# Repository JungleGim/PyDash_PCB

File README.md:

# PyDash_PCB - Information
This readme covers the printed circuit board or PCB portion of the PyDash. For the App design, Enclosure design, or OS design, see the below repositories:
- [PyDash_OS](https://github.com/JungleGim/PyDash_OS)
- [PyDash_App](https://github.com/JungleGim/PyDash_App)
- [PyDash_PCB](https://github.com/JungleGim/PyDash_PCB)
- [PyDash_Enclosure](https://github.com/JungleGim/PyDash_Enclosure)
- [PyDash_Builder](https://github.com/JungleGim/PyDash_Builder)

## Introduction
The PyDash_PCB is a daughter board that contains the hardware required for a rPi compute module (CM4) to function as a processor to display information on a 7in screen.

Additional details on the design considerations, required packages, and key features are included in the "Methodology" section of this readme.

# Project Status
## Revlog
- Rev 0: 06/02/2024
	- Initial issue
- Rev1a: 05/19/2025
	- Fixed button numbering to be appropriate when viewing the screen
- Rev2a: 02/15/2026
	- updates realted to Rev2.0a rebuild - includes new features and code architecture
	- Added micro SD socket for users to load dash config files
	- Updated USB port to USBC
	- Removed touch lines from screen and removed USB mux - no plans to utilize touch in future

# Methodology
## History
TBD: quick detail starting with the arduino + daughter board on the 5in display as a proof of concept

## Key Considerations and Constraints
The following sections are some notes on the various considerations or any constraints when designing the display.

### Power Supply
As built, with the sourced display and components in the BOM, the display uses approximately 350-400mA when operation, at 100% backlight.

### Display
The chosen display is a 7inch 1024x600 IPS display sourced from waveshare [link](https://www.waveshare.com/70h-1024600.htm?sku=22671). The display is fastened to the carrier PCB via double-sided foam tape. The 40pin FPC jack directly connects to the HDMI output from the CM4.

To control the backlight via PWM, drive the "BL_en" pin high. The PWM signal is scaled from 1024 (100%) to 0 (0) for brightest to darkest.

Any HDMI compatable display should be able to be used with this design. While the FPC cable was a design choice, any other HDMI connection should be appropriate, depending on the chosen display.

Additional considerations for the HDMI hardware and driver configuration is contained in the "PyDash OS" readme.

#### PCB stackup
JLC PCB stackups for TDMS impedence considerations

* Chosen stackup: JLC04121H-3313 – 1oz (0.035mm) outer layer
	+ Chosen stackup option
	+ Top to inner 1 and inner 2 to bot separation is 0.1
	+ requires 0.18mm trace width for single-ended impedence target
	+ 0.3mm separation for differential impedence target

* Other available options with calculated requirements
	+ JLC04121H-7628 - 1oz (0.035mm) outer layer
		* Top to inner 1 and inner 2 to bot separation is 0.2
		* requires 0.3mm trace width for single-ended impedence target
		* 0.25mm separation for differential impedence target
	+ JLC04121H-1080 Stackup – 1oz (0.035mm) outer layer
		* Top to inner 1 and inner 2 to bot separation is 0.0764
		* requires 0.13mm width
		* 0.20mm separation for differential impedence target

# Known bugs and bug fixes
No current known bugs

# FAQ section
No current FAQ

# Copyright and licensing information
## GNU GPLv3
This program is free software: you can redistribute it and/or modify it under the terms of the GNU General Public License as published by the Free Software Foundation, either version 3 of the License, or (at your option) any later version.

This program is distributed in the hope that it will be useful, but WITHOUT ANY WARRANTY; without even the implied warranty of MERCHANTABILITY or FITNESS FOR A PARTICULAR PURPOSE.  See the
GNU General Public License for more details.

You should have received a copy of the GNU General Public License along with this program.  If not, see <https://www.gnu.org/licenses/>.

## Additional disclaimer
The information included is provided "as is", without warranty of any kind, express or implied, including but not limited to the warranties of merchantability, fitness for a particular purpose and non-infringement. In no event shall the authors or copyright holders be liable for any claim, damages or other liability, whether in an action of contract, tort or otherwise, arising from, out of or in connection with the software or the use or other dealings in the software or tools included in this repository.

# General Notes and References
While I am an engineer by trade, my area of focus is not computer architecture or system engineering. Likely some people have already looked at various aspects of the codebase and just shook their heads. That being said, I've compiled a list of considerations and notes for the project that have helped me along the way. These are listed below, in no particular order.

## References
Throughout the project, I have used many references, related to various aspects/items of the project. These are all compiled in the list below, in no particular order
- TBD any notable references

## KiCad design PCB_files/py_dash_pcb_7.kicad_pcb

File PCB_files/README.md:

# PyDash_PCB - Information
This readme covers the printed circuit board or PCB portion of the PyDash. For the App design, Enclosure design, or OS design, see the below repositories:
- PyDash_OS
- PyDash_App
- PyDash_Enclosure

## Introduction
The PyDash_PCB is a daughter board that contains the hardware required for a rPi compute module (CM4) to function as a processor to display information on a 7in screen.

Additional details on the design considerations, required packages, and key features are included in the "Methodology" section of this readme.

# Project Status
## Revlog
- Rev 0: 06/02/2024
	- Initial issue
- Rev1a: 05/19/2025
	- Fixed button numbering to be appropriate when viewing the screen
- Rev2a: 02/15/2026
	- updates realted to Rev2.0a rebuild - includes new features and code architecture
	- Added micro SD socket for users to load dash config files
	- Updated USB port to USBC
	- Removed touch lines from screen and removed USB mux - no plans to utilize touch in future
	
## Future Development
The below is a list of wants/needs for future revisions; loosely listed in order of importance.

- USB port is routed but not functional; app design requires additional features
- Update mounting holes for CM4 to solder pads for use of solder-on standoffs to attach CM4
- Scope out board assembly cost

# Methodology
## History
TBD: quick detail starting with the arduino + daughter board on the 5in display as a proof of concept

## Key Considerations and Constraints
TBD: power supply and other notes (approx 350mA draw when running)
TBD: PWM backlight notes
TBD: display notes (especially different considerations)

# Known bugs and bug fixes
No current known bugs

# FAQ section
No current FAQ

# Copyright and licensing information
## GNU GPLv3
This program is free software: you can redistribute it and/or modify it under the terms of the GNU General Public License as published by the Free Software Foundation, either version 3 of the License, or (at your option) any later version.

This program is distributed in the hope that it will be useful, but WITHOUT ANY WARRANTY; without even the implied warranty of MERCHANTABILITY or FITNESS FOR A PARTICULAR PURPOSE.  See the
GNU General Public License for more details.

You should have received a copy of the GNU General Public License along with this program.  If not, see <https://www.gnu.org/licenses/>.

## Additional disclaimer
The information included is provided "as is", without warranty of any kind, express or implied, including but not limited to the warranties of merchantability, fitness for a particular purpose and non-infringement. In no event shall the authors or copyright holders be liable for any claim, damages or other liability, whether in an action of contract, tort or otherwise, arising from, out of or in connection with the software or the use or other dealings in the software or tools included in this repository.

# General Notes and References
While I am an engineer by trade, my area of focus is not computer architecture or system engineering. Likely some people have already looked at various aspects of the codebase and just shook their heads. That being said, I've compiled a list of considerations and notes for the project that have helped me along the way. These are listed below, in no particular order.

## References
Throughout the project, I have used many references, related to various aspects/items of the project. These are all compiled in the list below, in no particular order
- TBD any notable references

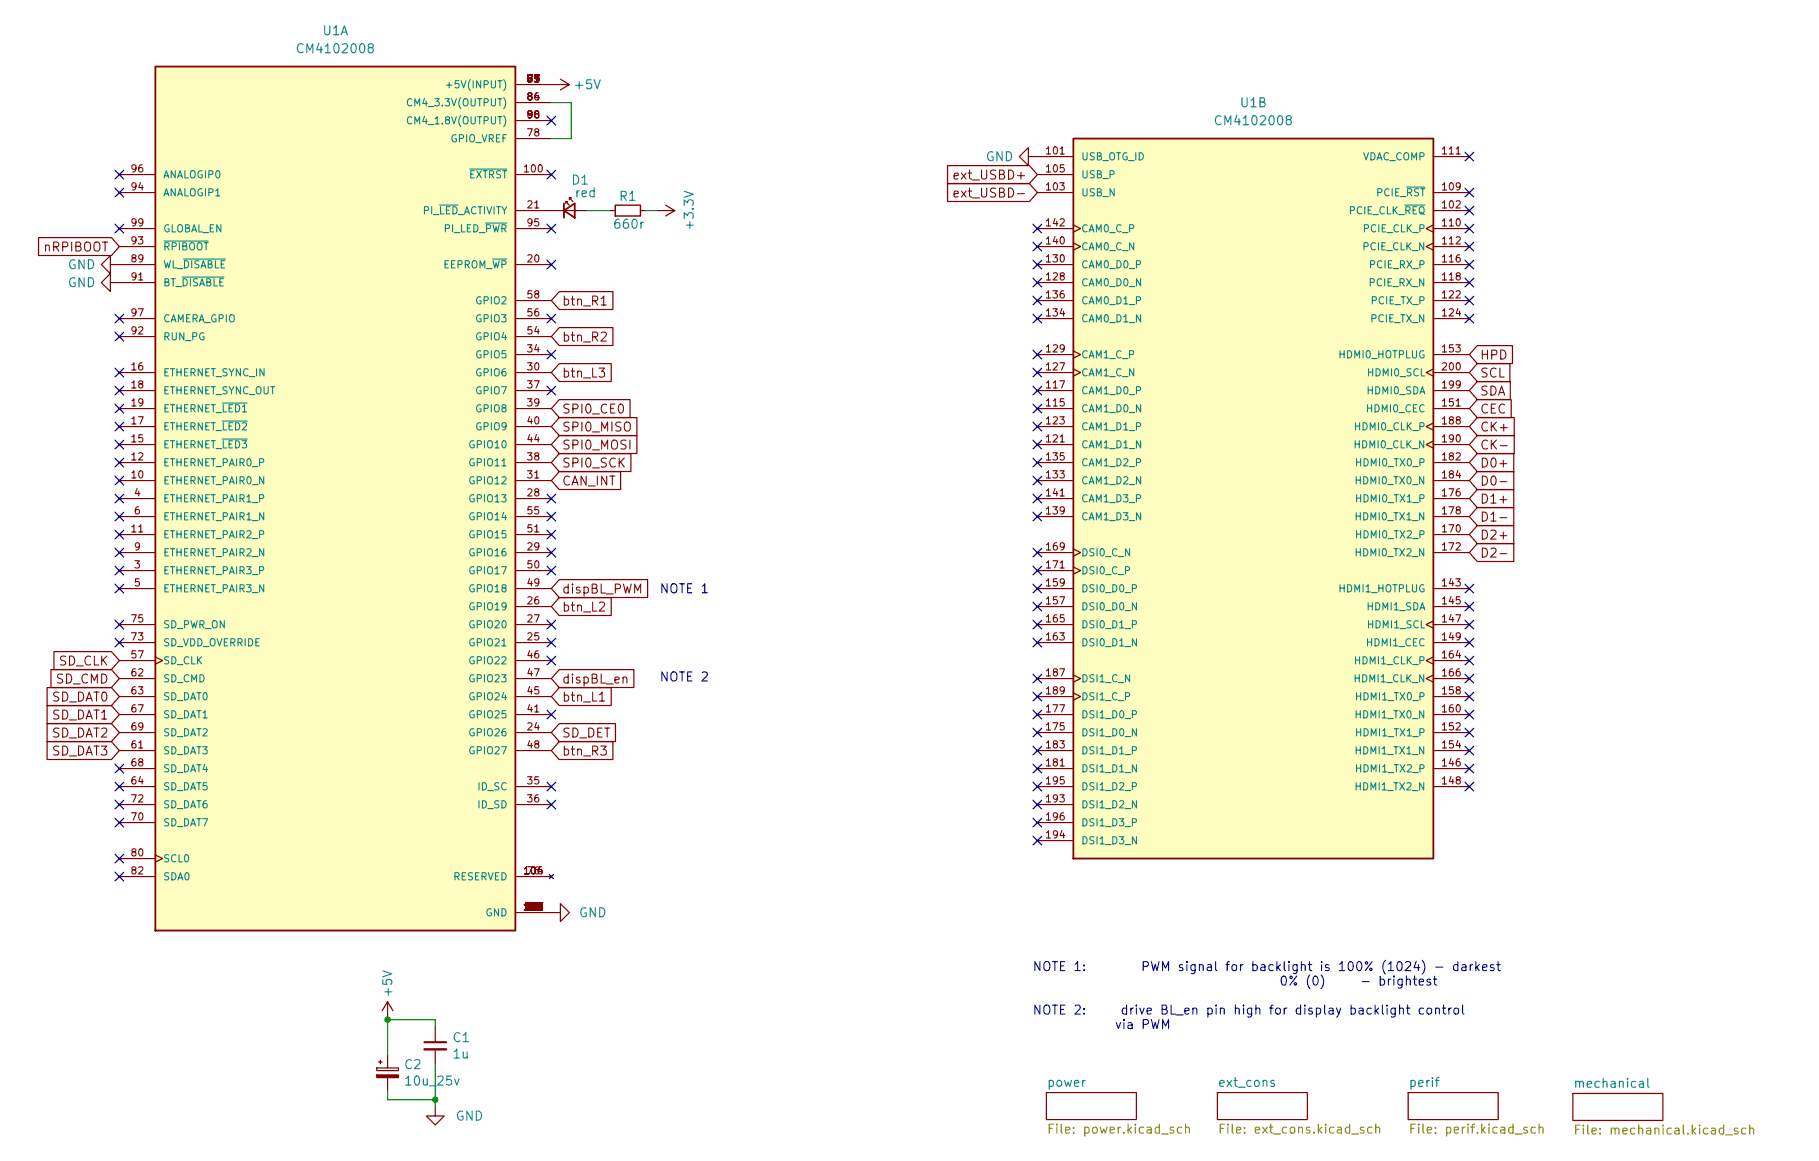
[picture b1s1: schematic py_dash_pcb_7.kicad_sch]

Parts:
C1: 1u; C_0805_2012Metric; MPN C0805C105M3RACTU
C2: 10u_25v; CP_EIA-3528-21_Kemet-B; MPN T495B106K025ATE750
D1: red; LED_0805_2012Metric; MPN 150080RS75000
R1: 660r; R_0805_2012Metric; MPN CRCW0805665RFKEA
U1: CM4102008; MODULE_CM4102008; PARTREV 2021-10-12

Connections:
+3.3V: R1.2; also elsewhere on the board
+5V: C1.1, C2.1, U1.77 (+5V(INPUT)), U1.79 (+5V(INPUT)), U1.81 (+5V(INPUT)), U1.83 (+5V(INPUT)), U1.85 (+5V(INPUT)), U1.87 (+5V(INPUT)); also elsewhere on the board
CAN_INT: U1.31 (GPIO12); also elsewhere on the board
CEC: U1.151 (HDMI0_CEC); also elsewhere on the board
CK+: U1.188 (HDMI0_CLK_P); also elsewhere on the board
CK-: U1.190 (HDMI0_CLK_N); also elsewhere on the board
D0+: U1.182 (HDMI0_TX0_P); also elsewhere on the board
D0-: U1.184 (HDMI0_TX0_N); also elsewhere on the board
D1+: U1.176 (HDMI0_TX1_P); also elsewhere on the board
D1-: U1.178 (HDMI0_TX1_N); also elsewhere on the board
D2+: U1.170 (HDMI0_TX2_P); also elsewhere on the board
D2-: U1.172 (HDMI0_TX2_N); also elsewhere on the board
GND: C1.2, C2.2, U1.1 (GND), U1.2 (GND), U1.7 (GND), U1.8 (GND), U1.13 (GND), U1.14 (GND), U1.22 (GND), U1.23 (GND), U1.32 (GND), U1.33 (GND), U1.42 (GND), U1.43 (GND), U1.52 (GND), U1.53 (GND), U1.59 (GND), U1.60 (GND), U1.65 (GND), U1.66 (GND), U1.71 (GND), U1.74 (GND), U1.89 (WL_~DISABLE), U1.91 (BT_~DISABLE), U1.98 (GND), U1.101 (USB_OTG_ID), U1.107 (GND), U1.108 (GND), U1.113 (GND), U1.114 (GND), U1.119 (GND), U1.120 (GND), U1.125 (GND), U1.126 (GND), U1.131 (GND), U1.132 (GND), U1.137 (GND), U1.138 (GND), U1.144 (GND), U1.150 (GND), U1.155 (GND), U1.156 (GND), U1.161 (GND), U1.162 (GND), U1.167 (GND), U1.168 (GND), U1.173 (GND), U1.174 (GND), U1.179 (GND), U1.180 (GND), U1.185 (GND), U1.186 (GND), U1.191 (GND), U1.192 (GND), U1.197 (GND), U1.198 (GND); also elsewhere on the board
HPD: U1.153 (HDMI0_HOTPLUG); also elsewhere on the board
unnamed: D1.2 (A), R1.1
unnamed: D1.1 (K), U1.21 (PI_~LED_ACTIVITY)
unnamed: U1.78 (GPIO_VREF), U1.84 (CM4_3.3V(OUTPUT)), U1.86 (CM4_3.3V(OUTPUT))
SCL: U1.200 (HDMI0_SCL); also elsewhere on the board
SDA: U1.199 (HDMI0_SDA); also elsewhere on the board
SD_CLK: U1.57 (SD_CLK); also elsewhere on the board
SD_CMD: U1.62 (SD_CMD); also elsewhere on the board
SD_DAT0: U1.63 (SD_DAT0); also elsewhere on the board
SD_DAT1: U1.67 (SD_DAT1); also elsewhere on the board
SD_DAT2: U1.69 (SD_DAT2); also elsewhere on the board
SD_DAT3: U1.61 (SD_DAT3); also elsewhere on the board
SD_DET: U1.24 (GPIO26); also elsewhere on the board
SPI0_CE0: U1.39 (GPIO8); also elsewhere on the board
SPI0_MISO: U1.40 (GPIO9); also elsewhere on the board
SPI0_MOSI: U1.44 (GPIO10); also elsewhere on the board
SPI0_SCK: U1.38 (GPIO11); also elsewhere on the board
btn_L1: U1.45 (GPIO24); also elsewhere on the board
btn_L2: U1.26 (GPIO19); also elsewhere on the board
btn_L3: U1.30 (GPIO6); also elsewhere on the board
btn_R1: U1.58 (GPIO2); also elsewhere on the board
btn_R2: U1.54 (GPIO4); also elsewhere on the board
btn_R3: U1.48 (GPIO27); also elsewhere on the board
dispBL_PWM: U1.49 (GPIO18); also elsewhere on the board
dispBL_en: U1.47 (GPIO23); also elsewhere on the board
ext_USBD+: U1.105 (USB_P); also elsewhere on the board
ext_USBD-: U1.103 (USB_N); also elsewhere on the board
nRPIBOOT: U1.93 (~RPIBOOT); also elsewhere on the board

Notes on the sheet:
NOTE 2
NOTE 1: PWM signal for backlight is 100% (1024) - darkest 0% (0) - brightest NOTE 2: drive BL_en pin high for display backlight control via PWM
NOTE 1

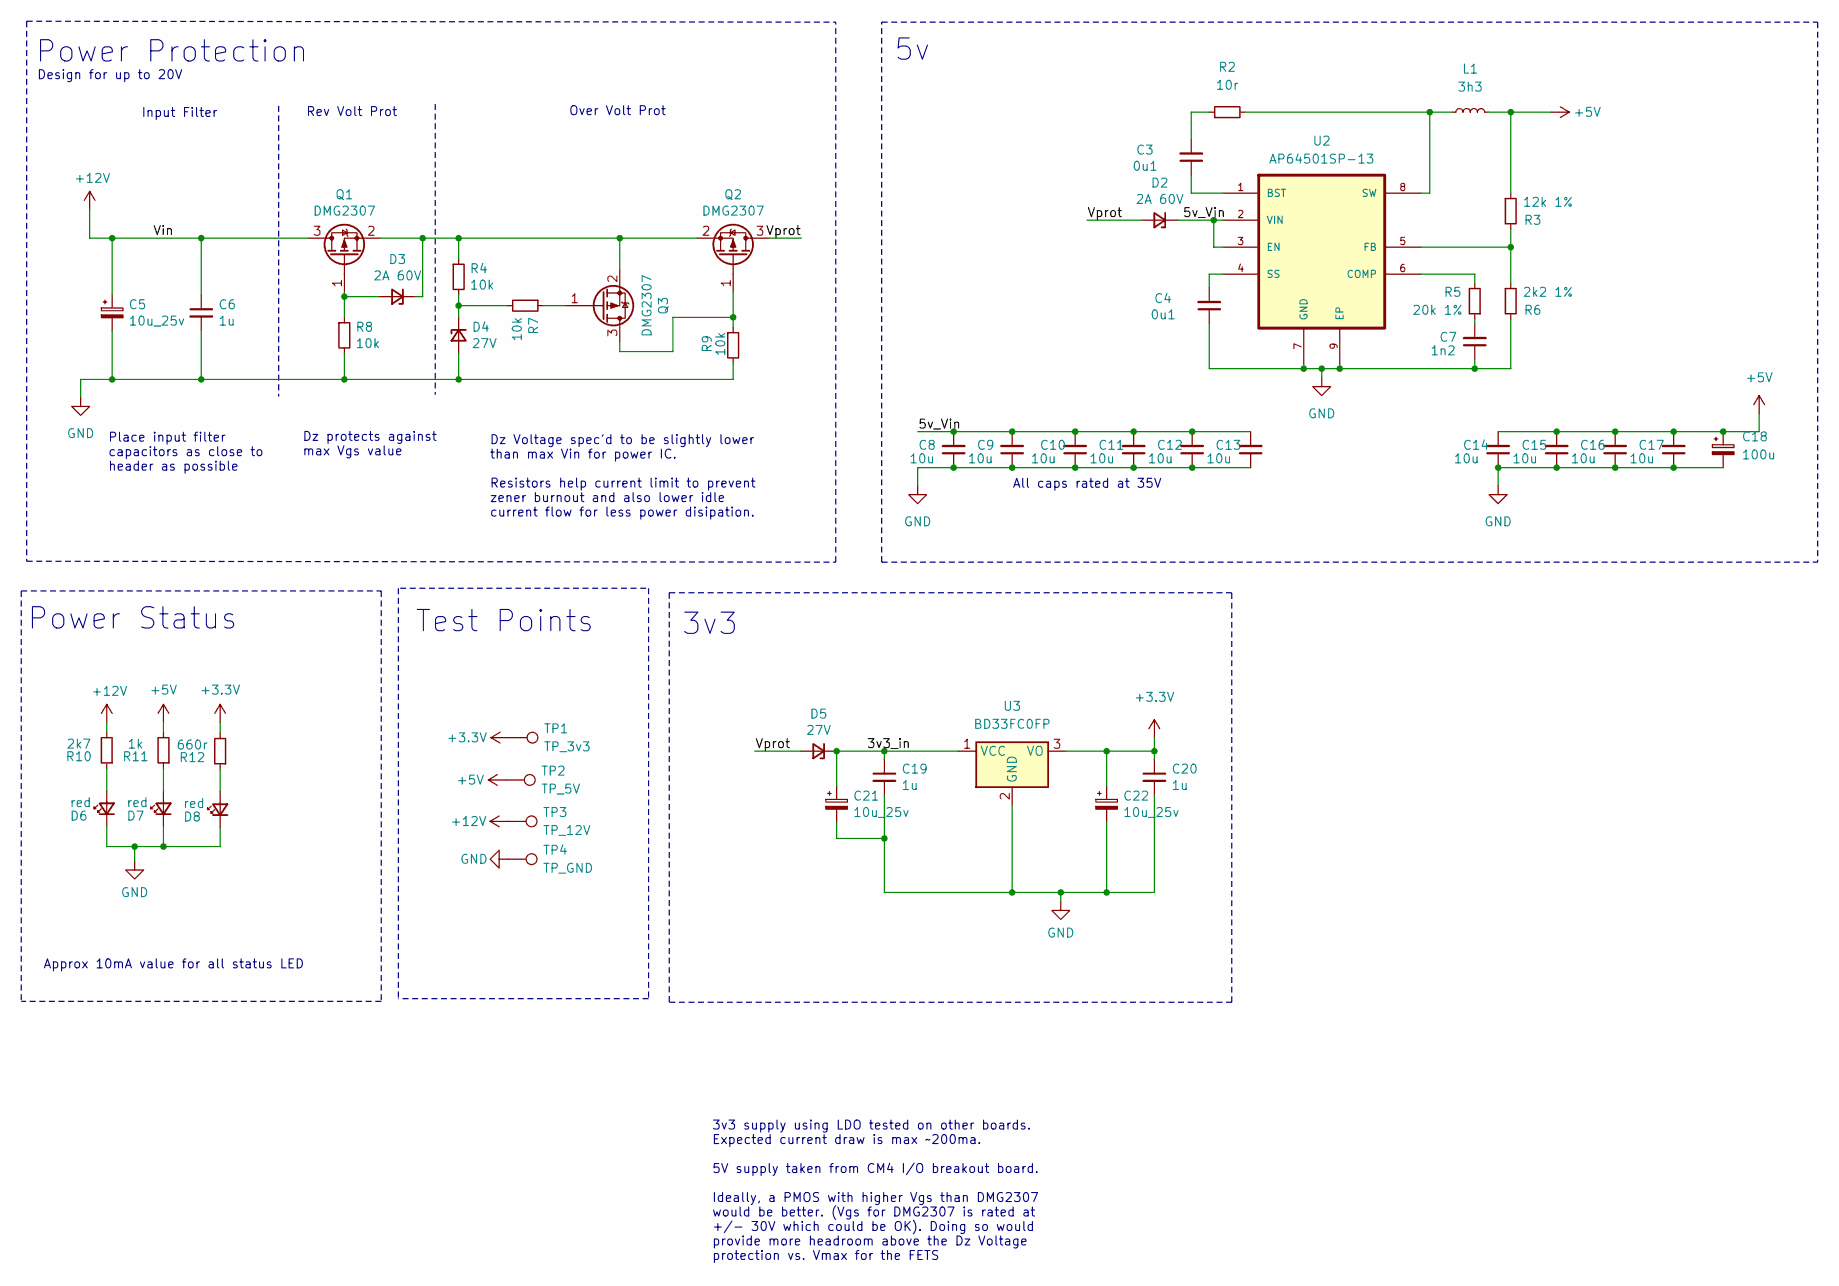
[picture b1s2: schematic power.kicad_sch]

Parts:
C3, C4: 0u1; C_0805_2012Metric; MPN C0805C104M5RACTU
C5, C21, C22: 10u_25v; CP_EIA-3528-21_Kemet-B; MPN T495B106K025ATE750
C6, C19, C20: 1u; C_0805_2012Metric; MPN C0805C105M3RACTU
C7: 1n2; C_0805_2012Metric; MPN C0805C122K5RACTU
C8, C9, C10, C11, C12, C13, C14, C15, C16, C17: 10u; C_0805_2012Metric; MPN C0805C106K4PAC
C18: 100u; CP_EIA-3528-21_Kemet-B; MPN TPSB107K010R0400
D2, D3: 2A 60V; D_SOD-123; MPN CDBMT260-HF
D4, D5: 27V; D_SOD-123; MPN MMSZ27T1G
D6, D7, D8: red; LED_0805_2012Metric; MPN 150080RS75000
L1: 3h3; L_Bourns_SRN6045TA; MPN SRN6045-3R3Y
Q1, Q2, Q3: DMG2307; SOT-23; MPN DMG2307L-7
R2: 10r; R_0805_2012Metric; MPN CRCW080510R0FKEA
R3: 12k 1%; R_0805_2012Metric; MPN CRCW080512K0FKTA
R4, R7, R8, R9: 10k; R_0805_2012Metric; MPN CRCW080510K0FKEA
R5: 20k 1%; R_0805_2012Metric; MPN CRCW080520K0FKEA
R6: 2k2 1%; R_0805_2012Metric; MPN CRCW08052K20FKEA
R10: 2k7; R_0805_2012Metric; MPN CRCW08052K70FKEA
R11: 1k; R_0805_2012Metric; MPN CRCW08051K00FKEA
R12: 660r; R_0805_2012Metric; MPN CRCW0805665RFKEA
TP1: TP_3v3; TestPoint_Pad_D1.0mm
TP2: TP_5V; TestPoint_Pad_D1.0mm
TP3: TP_12V; TestPoint_Pad_D1.0mm
TP4: TP_GND; TestPoint_Pad_D1.0mm
U2: AP64501SP-13; SOIC127P600X170-9N; MPN AP64501SP-13
U3: BD33FC0FP; TO-252-2; MPN NCV1117DT33T5G

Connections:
+3.3V: C20.1, C22.1, R12.2, TP1.1, U3.3 (VO); also elsewhere on the board
+5V: C14.2, C15.2, C16.2, C17.2, C18.1, L1.2, R3.1, R11.2, TP2.1; also elsewhere on the board
+12V: C5.1, C6.1, Q1.3 (D), R10.2, TP3.1; also elsewhere on the board
/power/3v3_in: C19.1, C21.1, D5.1 (K), U3.1 (VCC)
/power/5v_Vin: C8.2, C9.2, C10.2, C11.2, C12.2, C13.2, D2.1 (K), U2.2 (VIN), U2.3 (EN)
/power/Vprot: D2.2 (A), D5.2 (A), Q2.3 (D)
GND: C4.1, C5.2, C6.2, C7.1, C8.1, C9.1, C10.1, C11.1, C12.1, C13.1, C14.1, C15.1, C16.1, C17.1, C18.2, C19.2, C20.2, C21.2, C22.2, D4.2 (A), D6.1 (K), D7.1 (K), D8.1 (K), R6.2, R8.2, R9.2, TP4.1, U2.7 (GND), U2.9 (EP), U3.2 (GND); also elsewhere on the board
unnamed: C3.2, R2.1
unnamed: C7.2, R5.1
unnamed: D3.2 (A), Q1.1 (G), R8.1
unnamed: D3.1 (K), Q1.2 (S), Q2.2 (S), Q3.2 (S), R4.1
unnamed: D4.1 (K), R4.2, R7.2
unnamed: D6.2 (A), R10.1
unnamed: D7.2 (A), R11.1
unnamed: D8.2 (A), R12.1
unnamed: Q2.1 (G), Q3.3 (D), R9.1
unnamed: Q3.1 (G), R7.1
unnamed: C3.1, U2.1 (BST)
unnamed: R5.2, U2.6 (COMP)
unnamed: R3.2, R6.1, U2.5 (FB)
unnamed: C4.2, U2.4 (SS)
unnamed: L1.1, R2.2, U2.8 (SW)

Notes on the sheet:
Test Points
Place input filter capacitors as close to header as possible
Approx 10mA value for all status LED
Dz protects against max Vgs value
All caps rated at 35V
Design for up to 20V
Input Filter
3v3
Dz Voltage spec'd to be slightly lower than max Vin for power IC. Resistors help current limit to prevent zener burnout and also lower idle current flow for less power disipation.
Power Status
3v3 supply using LDO tested on other boards. Expected current draw is max ~200ma. 5V supply taken from CM4 I/O breakout board. Ideally, a PMOS with higher Vgs than DMG2307 would be better. (Vgs for DMG2307 is rated at +/- 30V which could be OK). Doing so would provide more headroom above the Dz Vol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
Rev Volt Prot
Over Volt Prot
Power Protection

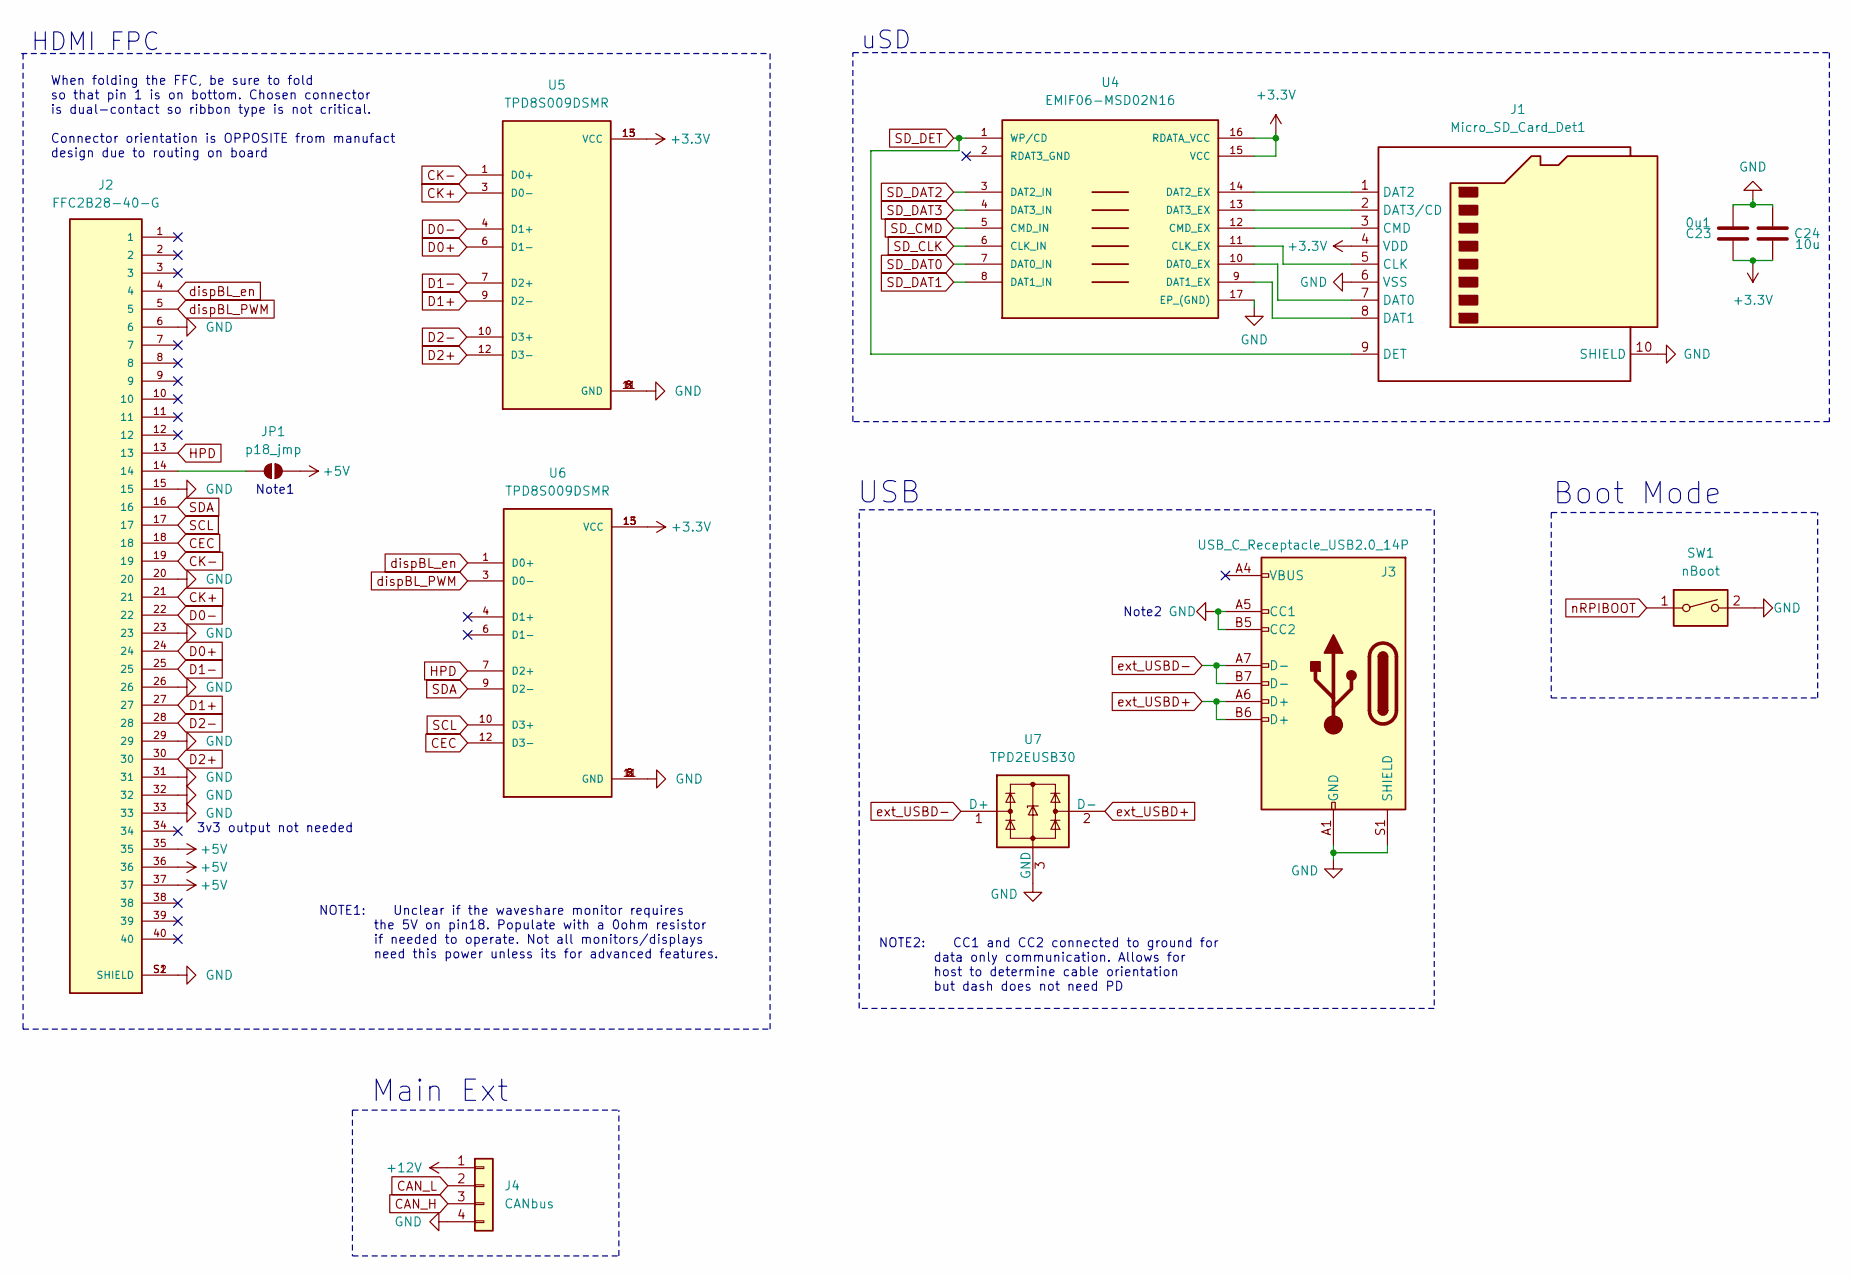
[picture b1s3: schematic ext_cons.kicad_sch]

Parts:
C23: 0u1; C_0805_2012Metric; MPN C0805C104M5RACTU
C24: 10u; C_0805_2012Metric; MPN C0805C106K4PAC
J1: Micro_SD_Card_Det1; microSD_HC_Hirose_DM3AT-SF-PEJM5; MPN DM3AT-SF-PEJM5(41)
J2: FFC2B28-40-G; GCT_FFC2B28-40-G; PARTREV A
J3: USB_C_Receptacle_USB2.0_14P; USB_C_Receptacle_GCT_USB4115-03-C; MPN USB4115-03-C
J4: CANbus; DT13-4P; MPN DTP10-4P
JP1: p18_jmp; SolderJumper-2_P1.3mm_Open_RoundedPad1.0x1.5mm
SW1: nBoot; SW_DIP_SPSTx01_Slide_6.7x4.1mm_W8.61mm_P2.54mm_LowProfile; MPN DS04-254-2-01BK-SMT
U4: EMIF06-MSD02N16; EMIF06MSD02N16; MOUSER_PART_NUMBER 511-EMIF06-MSD02N16
U5, U6: TPD8S009DSMR; IC_TPD8S009DSMR; PARTREV A
U7: TPD2EUSB30; Texas_DRT-3; MPN TPD2E009DRTR

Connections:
+3.3V: C23.1, C24.2, J1.4 (VDD), U4.15 (VCC), U4.16 (RDATA_VCC), U5.13 (VCC), U5.15 (VCC), U6.13 (VCC), U6.15 (VCC); also elsewhere on the board
+5V: J2.35, J2.36, J2.37, JP1.2 (B); also elsewhere on the board
+12V: J4.1; also elsewhere on the board
CAN_H: J4.3; also elsewhere on the board
CAN_L: J4.2; also elsewhere on the board
CEC: J2.18, U6.12 (D3-); also elsewhere on the board
CK+: J2.21, U5.3 (D0-); also elsewhere on the board
CK-: J2.19, U5.1 (D0+); also elsewhere on the board
D0+: J2.24, U5.6 (D1-); also elsewhere on the board
D0-: J2.22, U5.4 (D1+); also elsewhere on the board
D1+: J2.27, U5.9 (D2-); also elsewhere on the board
D1-: J2.25, U5.7 (D2+); also elsewhere on the board
D2+: J2.30, U5.12 (D3-); also elsewhere on the board
D2-: J2.28, U5.10 (D3+); also elsewhere on the board
GND: C23.2, C24.1, J1.6 (VSS), J1.10 (SHIELD), J2.6, J2.15, J2.20, J2.23, J2.26, J2.29, J2.31, J2.32, J2.33, J2.S1 (SHIELD), J2.S2 (SHIELD), J3.A1 (GND), J3.A5 (CC1), J3.A12 (GND), J3.B1 (GND), J3.B5 (CC2), J3.B12 (GND), J3.S1 (SHIELD), J4.4, SW1.2, U4.17 (EP_(GND)), U5.2 (GND), U5.5 (GND), U5.8 (GND), U5.11 (GND), U6.2 (GND), U6.5 (GND), U6.8 (GND), U6.11 (GND), U7.3 (GND); also elsewhere on the board
HPD: J2.13, U6.7 (D2+); also elsewhere on the board
unnamed: J1.5 (CLK), U4.11 (CLK_EX)
unnamed: J1.3 (CMD), U4.12 (CMD_EX)
unnamed: J1.7 (DAT0), U4.10 (DAT0_EX)
unnamed: J1.8 (DAT1), U4.9 (DAT1_EX)
unnamed: J1.1 (DAT2), U4.14 (DAT2_EX)
unnamed: J1.2 (DAT3/CD), U4.13 (DAT3_EX)
unnamed: J2.14, JP1.1 (A)
SCL: J2.17, U6.10 (D3+); also elsewhere on the board
SDA: J2.16, U6.9 (D2-); also elsewhere on the board
SD_CLK: U4.6 (CLK_IN); also elsewhere on the board
SD_CMD: U4.5 (CMD_IN); also elsewhere on the board
SD_DAT0: U4.7 (DAT0_IN); also elsewhere on the board
SD_DAT1: U4.8 (DAT1_IN); also elsewhere on the board
SD_DAT2: U4.3 (DAT2_IN); also elsewhere on the board
SD_DAT3: U4.4 (DAT3_IN); also elsewhere on the board
SD_DET: J1.9 (DET), U4.1 (WP/CD); also elsewhere on the board
dispBL_PWM: J2.5, U6.3 (D0-); also elsewhere on the board
dispBL_en: J2.4, U6.1 (D0+); also elsewhere on the board
ext_USBD+: J3.A6 (D+), J3.B6 (D+), U7.2 (D-); also elsewhere on the board
ext_USBD-: J3.A7 (D-), J3.B7 (D-), U7.1 (D+); also elsewhere on the board
nRPIBOOT: SW1.1; also elsewhere on the board

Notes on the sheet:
Main Ext
NOTE1: Unclear if the waveshare monitor requires the 5V on pin18. Populate with a 0ohm resistor if needed to operate. Not all monitors/displays need this power unless its for advanced features.
Note2
Boot Mode
When folding the FFC, be sure to fold so that pin 1 is on bottom. Chosen connector is dual-contact so ribbon type is not critical. Connector orientation is OPPOSITE from manufact design due to routing on board
uSD
NOTE2: CC1 and CC2 connected to ground for data only communication. Allows for host to determine cable orientation but dash does not need PD
Note1
USB
HDMI FPC
3v3 output not needed

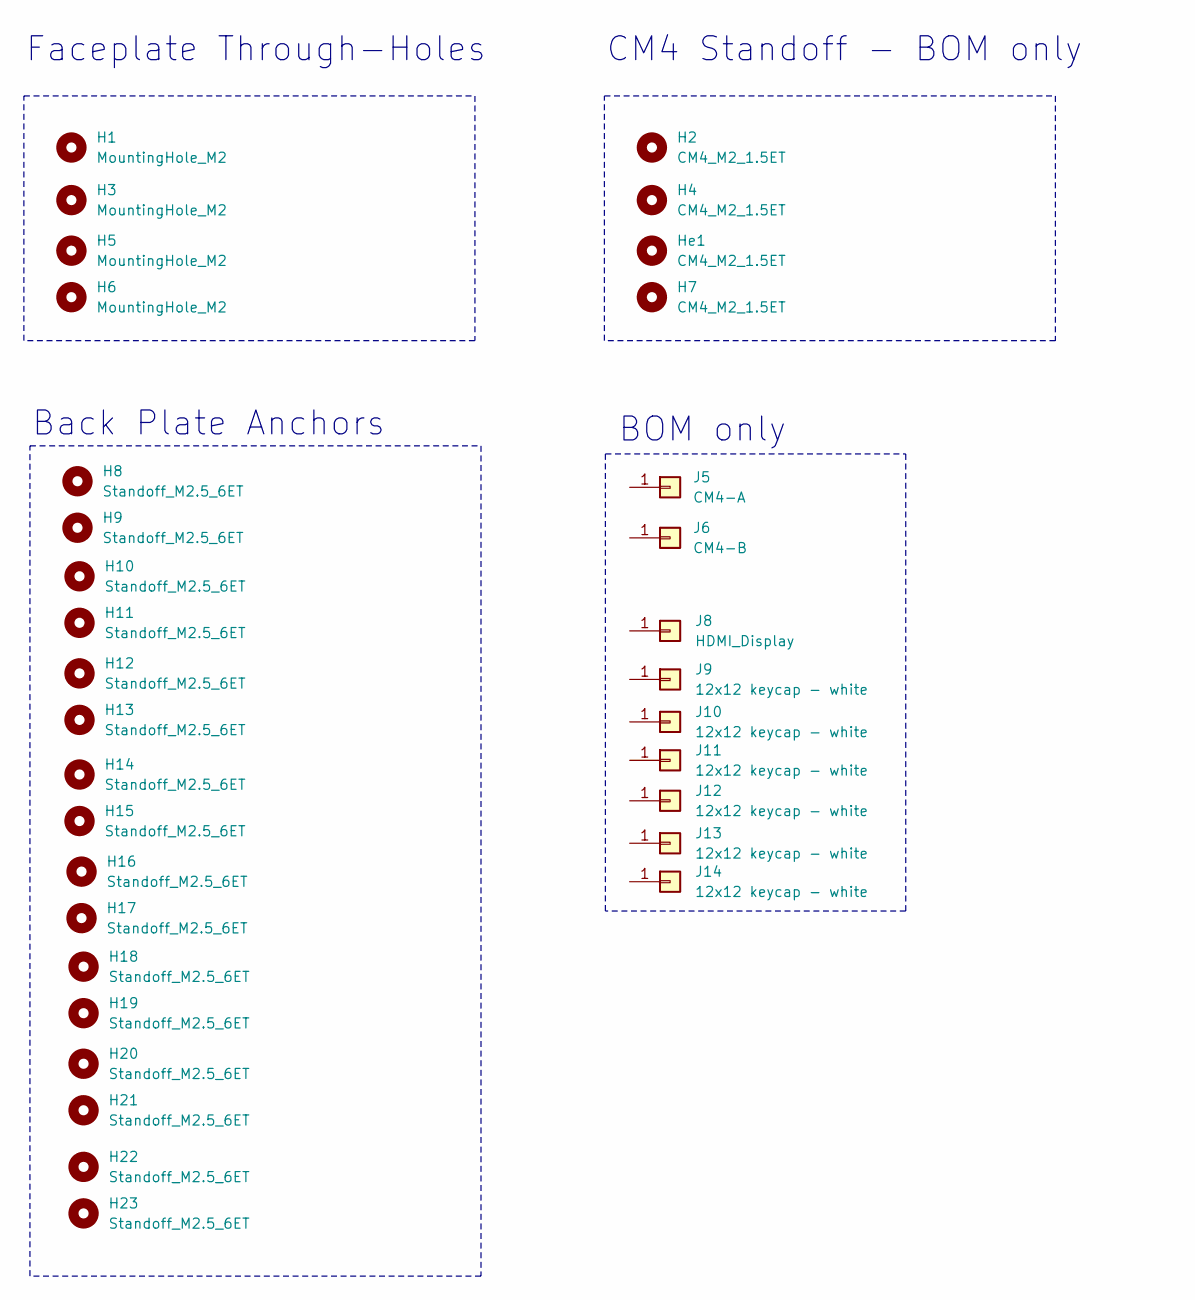
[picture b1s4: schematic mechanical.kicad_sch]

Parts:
H1, H3, H5, H6: MountingHole_M2; MountingHole_3.2mm_M3_DIN965_Pad_TopOnly
H2, H4, H7: CM4_M2_1.5ET; MountingHole_3.2mm_M3_DIN965_Pad_TopOnly; MPN 9774015243R
H8, H9, H10, H11, H12, H13, H14, H15, H16, H17, H18, H19, H20, H21, H22, H23: Standoff_M2.5_6ET; MPN SMTSO-M25-6ET
He1: CM4_M2_1.5ET; MountingHole_3.2mm_M3_DIN965_Pad_TopOnly; MPN 9774015243R
J5: CM4-A; N/A; MPN DF40C-100DS-0.4V(51)
J6: CM4-B; N/A; MPN DF40C-100DS-0.4V(51)
J8: HDMI_Display; N/A; MPN 70H-1024600-IPS-A
J9, J10, J11, J12, J13, J14: 12x12 keycap - white; N/A; MPN B32-1360

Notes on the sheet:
Back Plate Anchors
BOM only
Faceplate Through-Holes
CM4 Standoff - BOM only

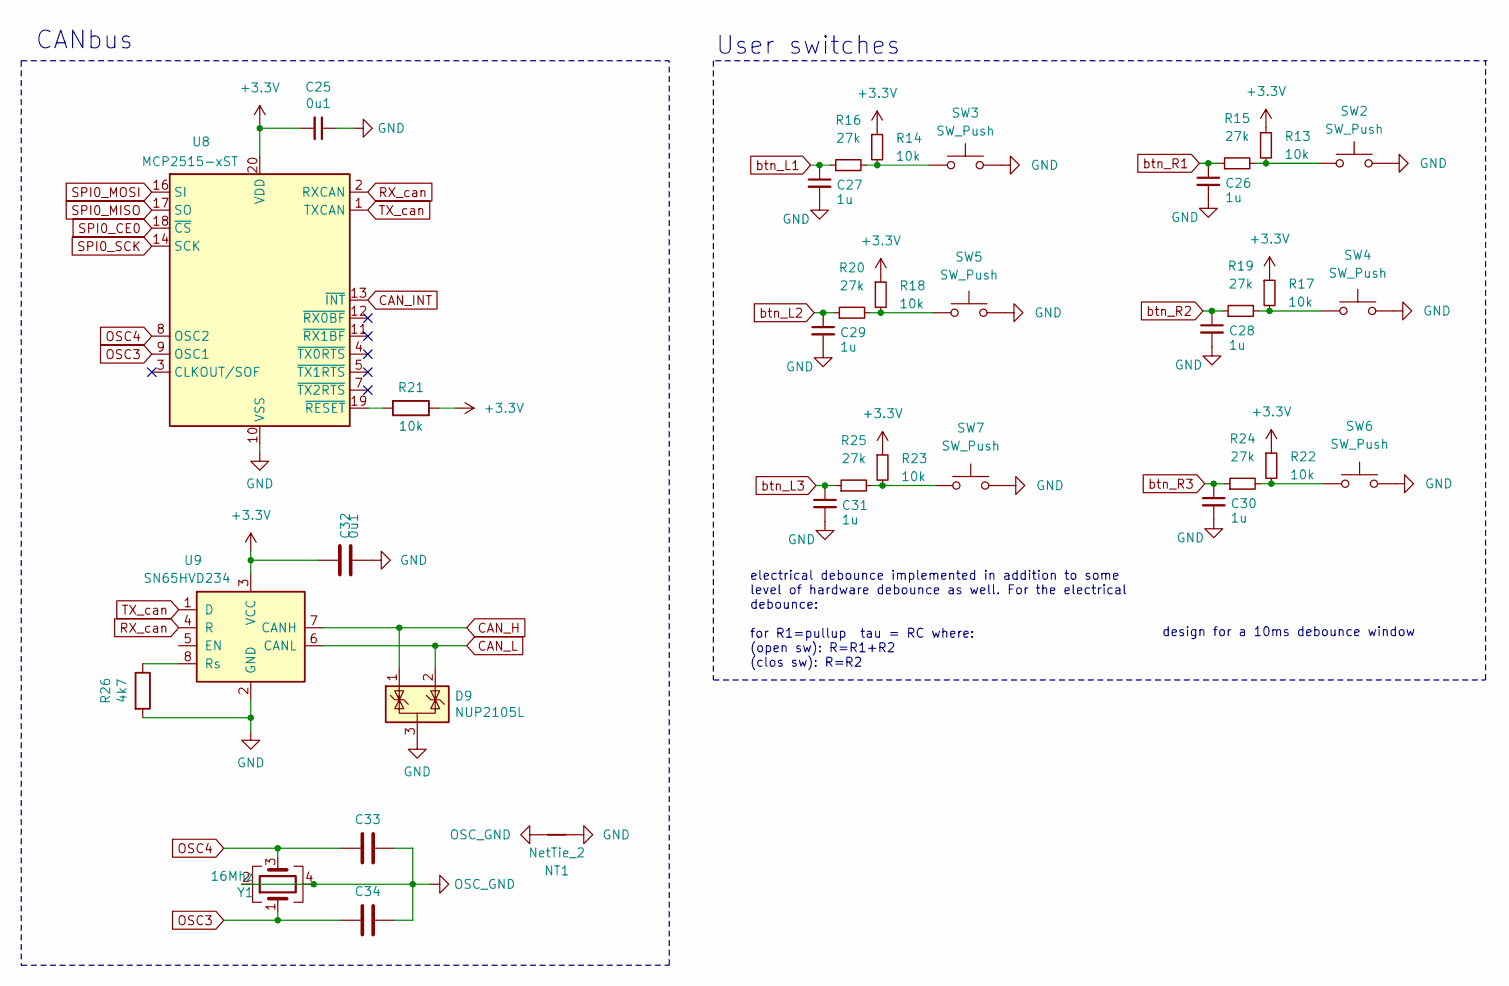
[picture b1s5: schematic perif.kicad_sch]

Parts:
C25, C32: 0u1; C_0805_2012Metric; MPN C0805C104M5RACTU
C26, C27, C28, C29, C30, C31: 1u; C_0805_2012Metric; MPN C0805C105M3RACTU
C33, C34: 20p; C_0805_2012Metric; MPN C0805C200F5GACTU
D9: NUP2105L; SOT-23; MPN NUP2105LT1G
NT1: NetTie_2; NetTie-2_SMD_Pad0.2mm
R13, R14, R17, R18, R21, R22, R23: 10k; R_0805_2012Metric; MPN CRCW080510K0FKEA
R15, R16, R19, R20, R24, R25: 27k; R_0805_2012Metric; MPN CRCW080527K0FKEA
R26: 4k7; R_0805_2012Metric; MPN CRCW08054K70FKEA
SW2, SW3, SW4, SW5, SW6, SW7: SW_Push; SW_B3F-4050_OMR; MPN B3F-5050
U8: MCP2515-xST; TSSOP-20_4.4x6.5mm_P0.65mm; MPN MCP2515T-E/ST
U9: SN65HVD234; SOIC-8_3.9x4.9mm_P1.27mm; MPN SN65HVD234DR
Y1: 16Mhz; Crystal_SMD_3225-4Pin_3.2x2.5mm; MPN FA-238 16.0000MB-C3

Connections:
+3.3V: C25.2, C32.1, R13.1, R14.1, R17.1, R18.1, R21.1, R22.1, R23.1, U8.20 (VDD), U9.3 (VCC); also elsewhere on the board
CAN_H: D9.1 (K), U9.7 (CANH); also elsewhere on the board
CAN_INT: U8.13 (~INT); also elsewhere on the board
CAN_L: D9.2 (K), U9.6 (CANL); also elsewhere on the board
GND: C25.1, C26.2, C27.2, C28.2, C29.2, C30.2, C31.2, C32.2, D9.3 (A), NT1.1, R26.2, SW2.3 (2), SW3.3 (2), SW4.3 (2), SW5.3 (2), SW6.3 (2), SW7.3 (2), U8.10 (VSS), U9.2 (GND); also elsewhere on the board
unnamed: R13.2, R15.2, SW2.1
unnamed: R14.2, R16.2, SW3.1
unnamed: R17.2, R19.2, SW4.1
unnamed: R18.2, R20.2, SW5.1
unnamed: R22.2, R24.2, SW6.1
unnamed: R23.2, R25.2, SW7.1
unnamed: R21.2, U8.19 (~RESET)
unnamed: R26.1, U9.8 (Rs)
OSC3: C34.2, U8.9 (OSC1), Y1.1
OSC4: C33.2, U8.8 (OSC2), Y1.3
OSC_GND: C33.1, C34.1, NT1.2, Y1.2, Y1.4
RX_can: U8.2 (RXCAN), U9.4 (R)
SPI0_CE0: U8.18 (~CS); also elsewhere on the board
SPI0_MISO: U8.17 (SO); also elsewhere on the board
SPI0_MOSI: U8.16 (SI); also elsewhere on the board
SPI0_SCK: U8.14 (SCK); also elsewhere on the board
TX_can: U8.1 (TXCAN), U9.1 (D)
btn_L1: C27.1, R16.1; also elsewhere on the board
btn_L2: C29.1, R20.1; also elsewhere on the board
btn_L3: C31.1, R25.1; also elsewhere on the board
btn_R1: C26.1, R15.1; also elsewhere on the board
btn_R2: C28.1, R19.1; also elsewhere on the board
btn_R3: C30.1, R24.1; also elsewhere on the board

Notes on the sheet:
electrical debounce implemented in addition to some level of hardware debounce as well. For the electrical debounce: for R1=pullup tau = RC where: (open sw): R=R1+R2 (clos sw): R=R2
User switches
CANbus
design for a 10ms debounce window
